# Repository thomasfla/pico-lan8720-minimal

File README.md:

# pico-lan8720-minimal
Pi pico / Pi pico2 hat with LAN8720 Ethernet PHY wihtout MDIO

[View PCB online](https://kicanvas.org/?github=https%3A%2F%2Fgithub.com%2Fthomasfla%2Fpico-lan8720-minimal)

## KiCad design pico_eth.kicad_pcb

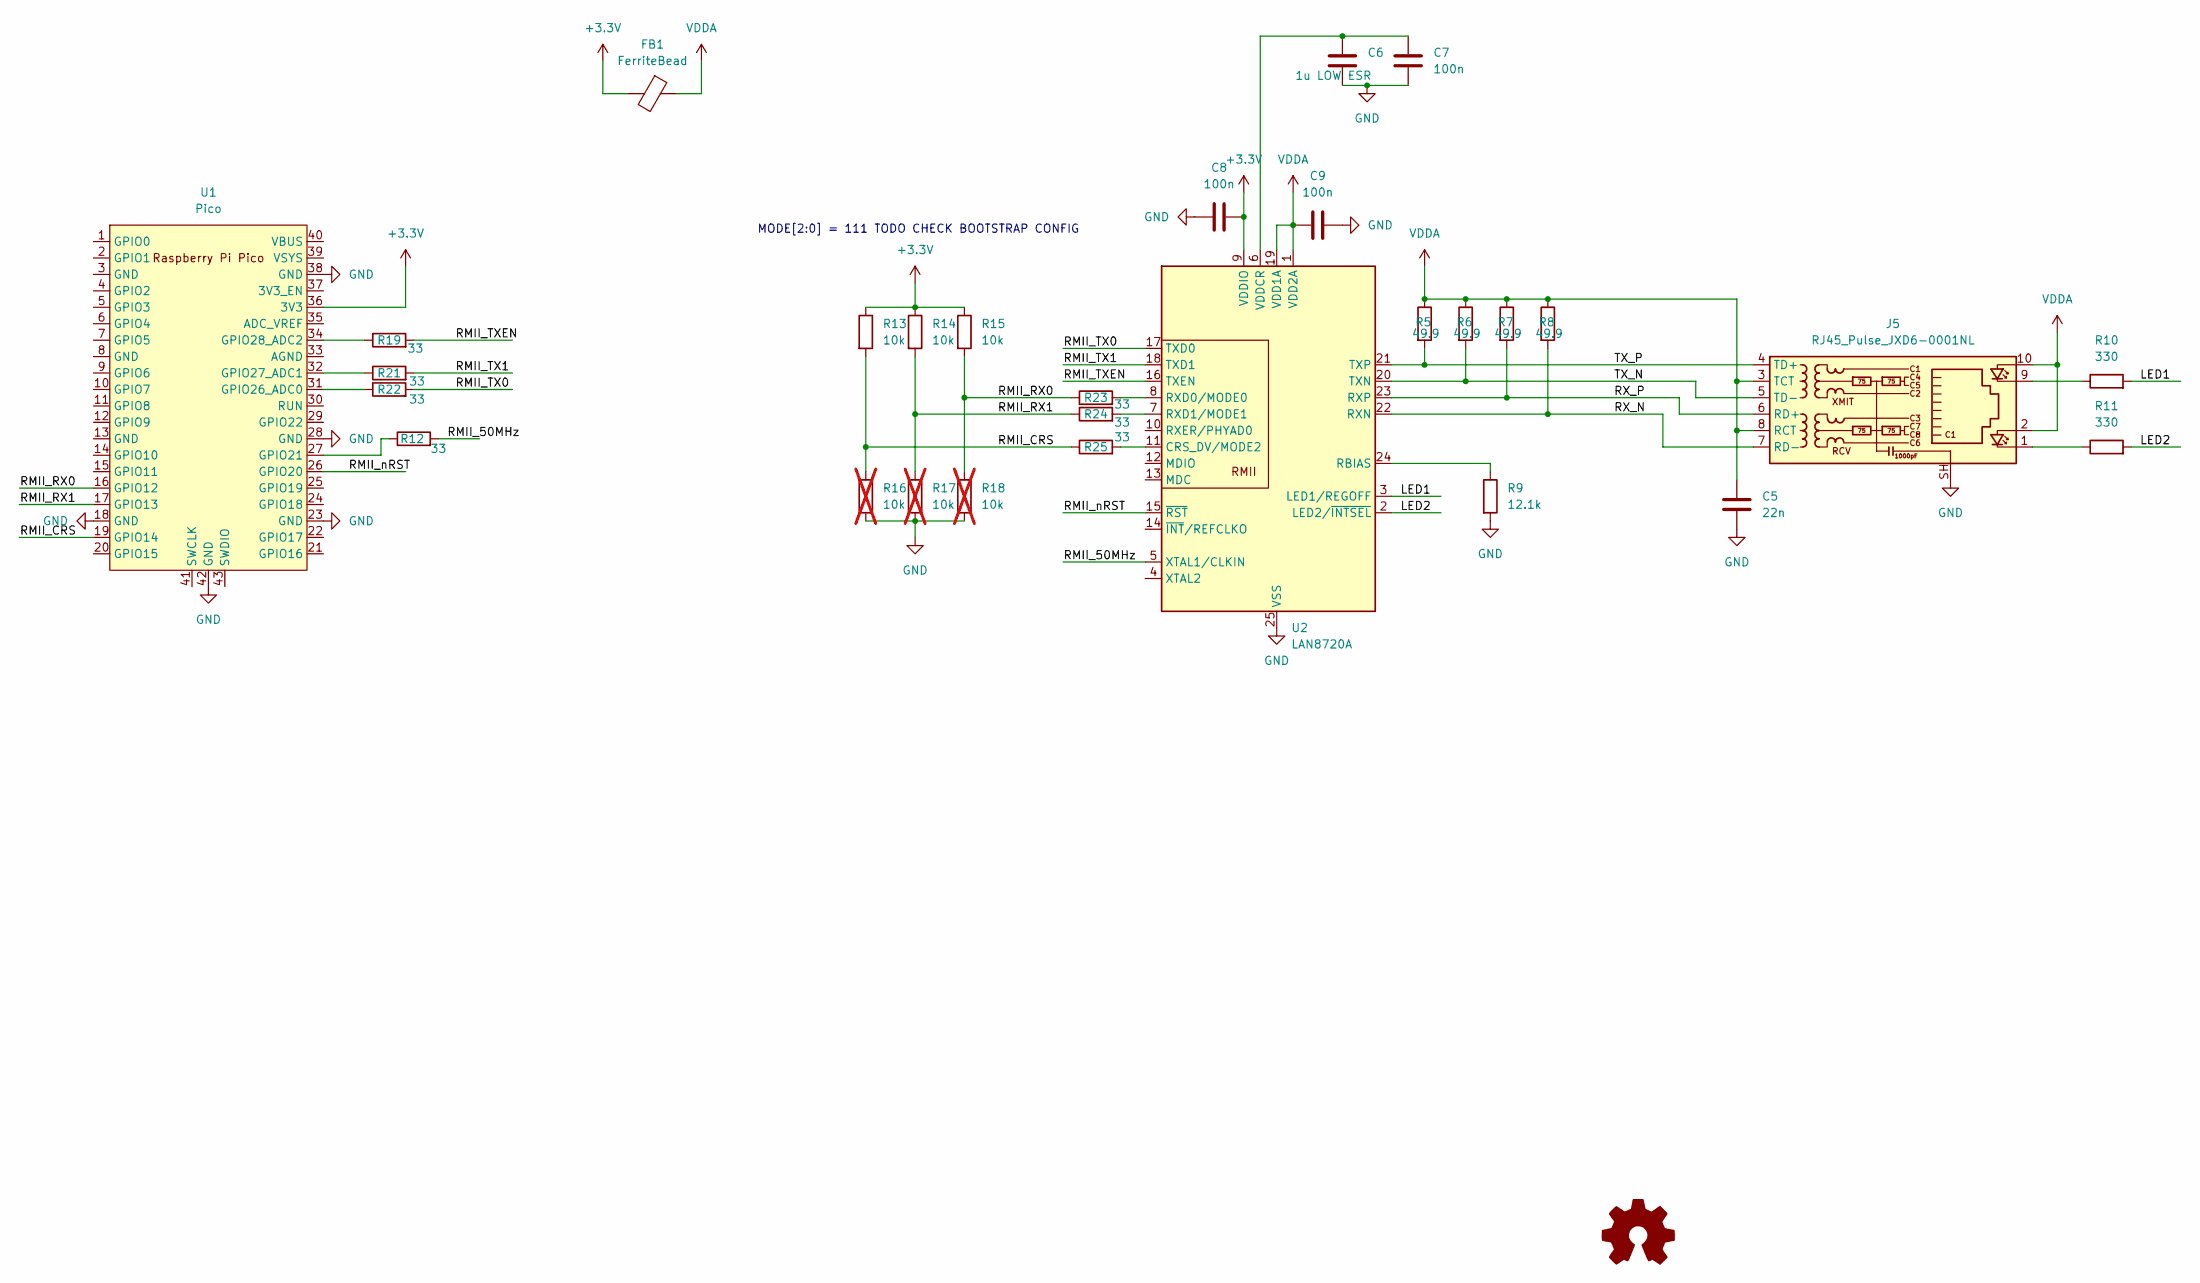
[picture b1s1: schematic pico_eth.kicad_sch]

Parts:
C5: 22n; C_0402_1005Metric
C6: 1u LOW ESR; C_0402_1005Metric
C7, C8, C9: 100n; C_0402_1005Metric
FB1: FerriteBead; L_0402_1005Metric
J5: RJ45_Pulse_JXD6-0001NL; RJ45_Pulse_JXD6-0001NL_Horizontal
R5, R6, R7, R8: 49.9; R_0402_1005Metric
R9: 12.1k; R_0402_1005Metric
R10, R11: 330; R_0402_1005Metric
R12, R19, R21, R22, R23, R24, R25: 33; R_0402_1005Metric
R13, R14, R15: 10k; R_0402_1005Metric
R16, R17, R18: 10k; R_0402_1005Metric; not fitted
U1: Pico; RPi_Pico_SMD_TH
U2: LAN8720A; VQFN-24-1EP_4x4mm_P0.5mm_EP2.5x2.5mm_ThermalVias

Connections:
+3.3V: C8.2, FB1.2, R13.1, R14.1, R15.1, U1.36 (3V3), U2.9 (VDDIO)
/LED1: R10.2, U2.3 (LED1/REGOFF)
/LED2: R11.2, U2.2 (LED2/~INTSEL)
/OE0: U1.2 (GPIO1)
/OE1: U1.6 (GPIO4)
/OE2: U1.10 (GPIO7)
/OE3: U1.14 (GPIO10)
/RMII_50MHz: R12.2, U2.5 (XTAL1/CLKIN)
/RMII_CRS: R13.2, R16.1, R25.1, U1.19 (GPIO14)
/RMII_RX0: R15.2, R18.1, R23.1, U1.16 (GPIO12)
/RMII_RX1: R14.2, R17.1, R24.1, U1.17 (GPIO13)
/RMII_TX0: R22.2, U2.17 (TXD0)
/RMII_TX1: R21.2, U2.18 (TXD1)
/RMII_TXEN: R19.2, U2.16 (TXEN)
/RMII_nRST: U1.26 (GPIO20), U2.15 (~RST)
/RX0: U1.4 (GPIO2)
/RX1: U1.7 (GPIO5)
/RX2: U1.11 (GPIO8)
/RX3: U1.15 (GPIO11)
/RX_N: J5.7 (RD-), R8.2, U2.22 (RXN)
/RX_P: J5.6 (RD+), R7.2, U2.23 (RXP)
/TX0: U1.1 (GPIO0)
/TX1: U1.5 (GPIO3)
/TX2: U1.9 (GPIO6)
/TX3: U1.12 (GPIO9)
/TX_N: J5.5 (TD-), R6.2, U2.20 (TXN)
/TX_P: J5.4 (TD+), R5.2, U2.21 (TXP)
GND: C5.2, C6.2, C7.2, C8.1, C9.2, J5.SH, R9.2, R16.2, R17.2, R18.2, U1.3 (GND), U1.8 (GND), U1.13 (GND), U1.18 (GND), U1.23 (GND), U1.28 (GND), U1.38 (GND), U1.42 (GND), U2.25 (VSS)
unnamed: J5.1, R11.1
unnamed: J5.9, R10.1
unnamed: R12.1, U1.27 (GPIO21)
unnamed: R22.1, U1.31 (GPIO26_ADC0)
unnamed: R21.1, U1.32 (GPIO27_ADC1)
unnamed: R19.1, U1.34 (GPIO28_ADC2)
unnamed: R25.2, U2.11 (CRS_DV/MODE2)
unnamed: R9.1, U2.24 (RBIAS)
unnamed: R23.2, U2.8 (RXD0/MODE0)
unnamed: R24.2, U2.7 (RXD1/MODE1)
unnamed: C6.1, C7.1, U2.6 (VDDCR)
VDDA: C5.1, C9.1, FB1.1, J5.2, J5.3 (TCT), J5.8 (RCT), J5.10, R5.1, R6.1, R7.1, R8.1, U2.1 (VDD2A), U2.19 (VDD1A)

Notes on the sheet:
MODE[2:0] = 111 TODO CHECK BOOTSTRAP CONFIG

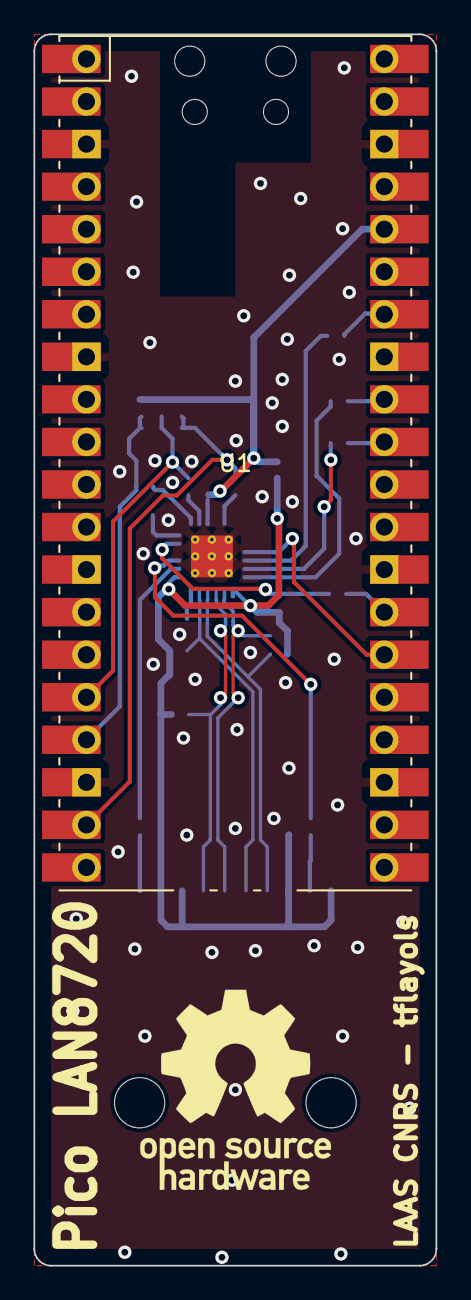
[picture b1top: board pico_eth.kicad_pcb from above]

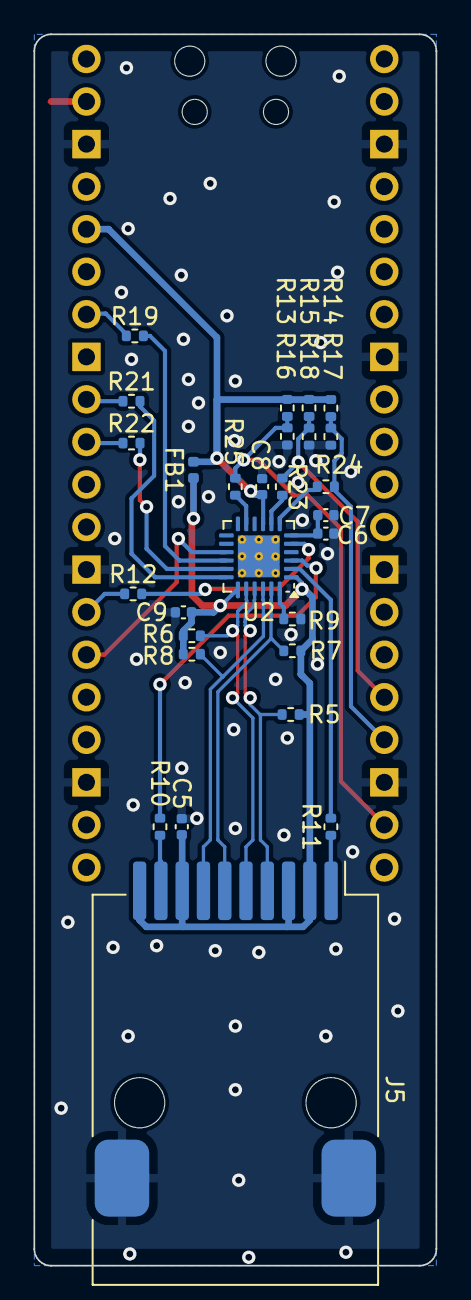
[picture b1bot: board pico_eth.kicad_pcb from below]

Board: 2 copper layers, 24.0 x 73.5 mm, 29 parts (28 on the bottom side), 28 nets.

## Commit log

2025-06-02 Add design files
2025-06-02 add picture and update readme
2025-06-02 Add picture
